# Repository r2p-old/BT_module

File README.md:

Bluetooth module 
==========

The R2P Bluetooth module.

### Hardware

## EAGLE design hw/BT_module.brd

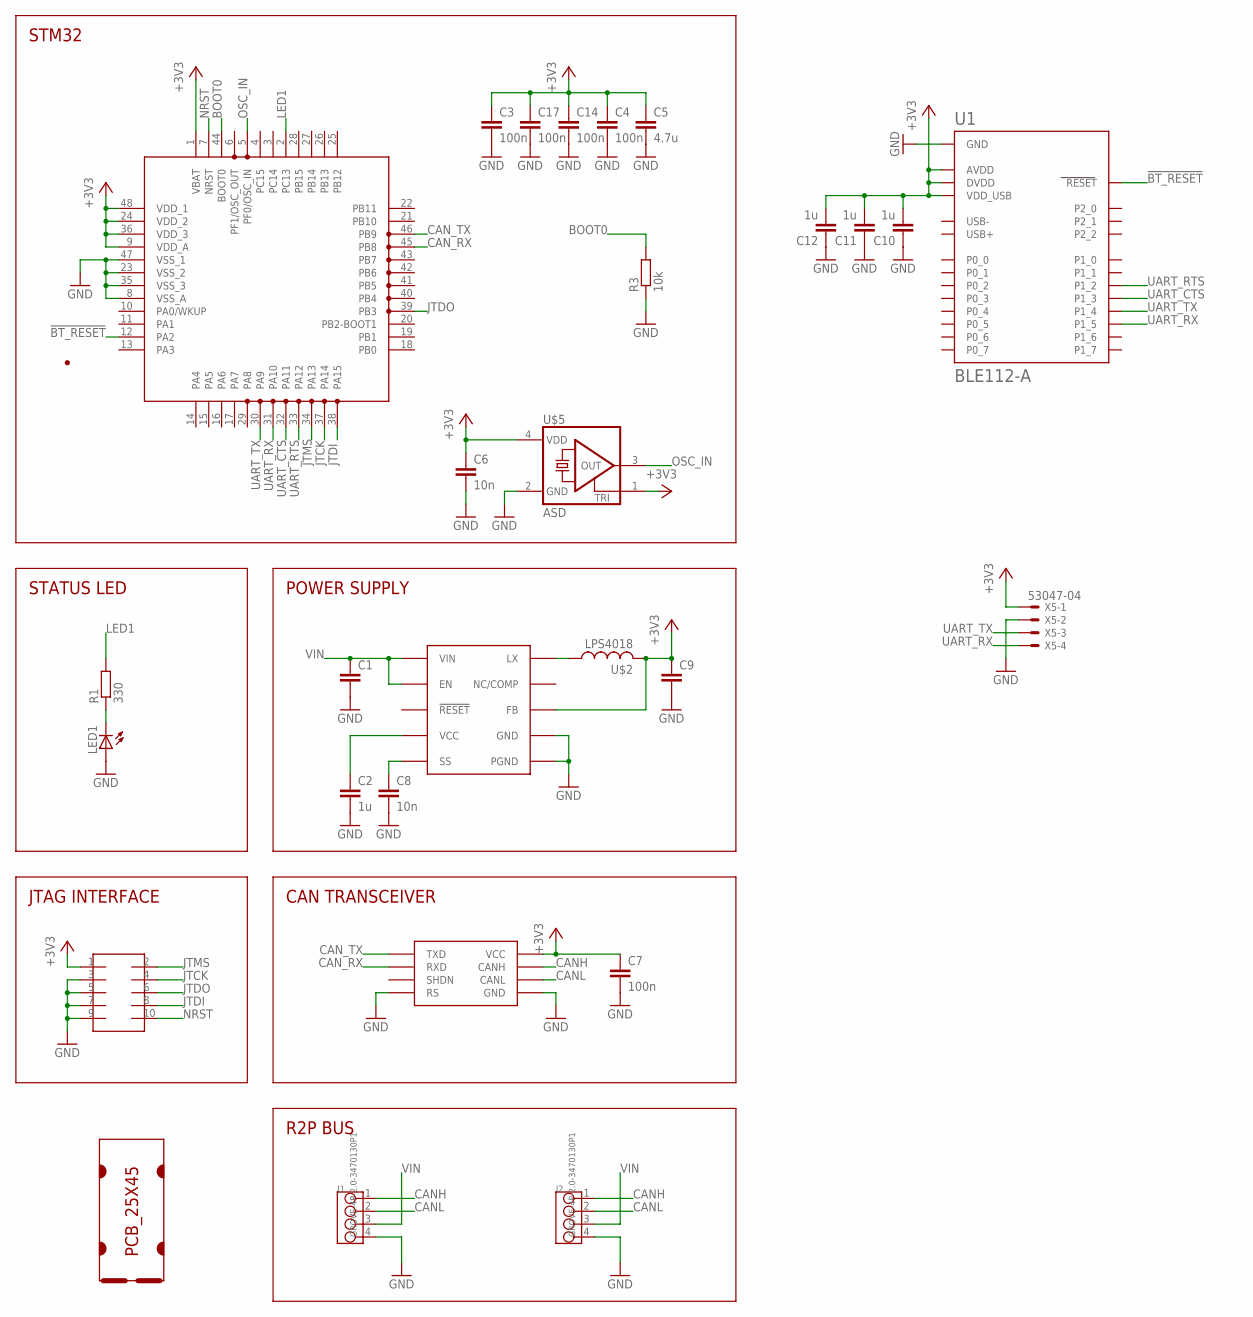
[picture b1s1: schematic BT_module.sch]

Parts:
C1: C-EUC1206; C1206
C2, C10, C11, C12: 1u; C0603
C3, C4, C7, C14, C17: 100n; C0603
C5: 4.7u; C0805
C6, C8: 10n; C0603
C9: C-EUC0805; C0805
J1, J2: GROVE-4P-2.0-3470130P1; 4P-2.0
LED1: LEDCHIPLED_0805; CHIPLED_0805
R1: 330; R0603
R3: 10k; R0603
SOT1: MAX3051EKA; SOT23-8L
U1: BLE112-A
U$1: PCB_25X45; 25X45
U$2: LPS4018
U$3: MAX17501; TDFN-10
U$4: FTSH-105TH; FTSH-105-TH
U$5: ASD; 2.5X2
U$6: STM32F303C; LQFP48
X5: 53047-04

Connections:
!BT_RESET: U1.RESET, U$6.12 (PA2)
+3V3: C3.1, C4.1, C5.1, C6.1, C7.1, C9.1, C10.2, C11.2, C12.2, C14.1, C17.1, SOT1.3 (VCC), U1.AVDD, U1.AVDD@2 (AVDD), U1.DVDD, U1.VDD_USB, U$2.P$2 (2), U$3.P$5 (FB), U$4.1, U$5.1 (TRI), U$5.4 (VDD), U$6.1 (VBAT), U$6.9 (VDD_A), U$6.24 (VDD_2), U$6.36 (VDD_3), U$6.48 (VDD_1), X5.1
BOOT0: R3.2, U$6.44 (BOOT0)
CANH: J1.1, J2.1, SOT1.7 (CANH)
CANL: J1.2, J2.2, SOT1.6 (CANL)
CAN_RX: SOT1.4 (RXD), U$6.45 (PB8)
CAN_TX: SOT1.1 (TXD), U$6.46 (PB9)
GND: C1.2, C2.2, C3.2, C4.2, C5.2, C6.2, C7.2, C8.2, C9.2, C10.1, C11.1, C12.1, C14.2, C17.2, J1.4, J2.4, LED1.A, R3.1, SOT1.2 (GND), SOT1.8 (RS), U1.GND, U1.GND@2 (GND), U1.GND@3 (GND), U1.GND@4 (GND), U$3.P$1 (PGND), U$3.P$9 (GND), U$3.P$11 (PGND), U$4.3, U$4.5, U$4.7, U$4.9, U$5.2 (GND), U$6.8 (VSS_A), U$6.23 (VSS_2), U$6.35 (VSS_3), U$6.47 (VSS_1), X5.2
JTCK: U$4.4, U$6.37 (PA14)
JTDI: U$4.8, U$6.38 (PA15)
JTDO: U$4.6, U$6.39 (PB3)
JTMS: U$4.2, U$6.34 (PA13)
LED1: R1.2, U$6.2 (PC13)
unnamed: U$2.P$1 (1), U$3.P$10 (LX)
unnamed: LED1.C, R1.1
unnamed: C2.1, U$3.P$4 (VCC)
unnamed: C8.1, U$3.P$6 (SS)
NRST: U$4.10, U$6.7 (NRST)
OSC_IN: U$5.3 (OUT), U$6.5 (PF0/OSC_IN)
UART_CTS: U1.P1_3, U$6.32 (PA11)
UART_RTS: U1.P1_2, U$6.33 (PA12)
UART_RX: U1.P1_5, U$6.31 (PA10), X5.4
UART_TX: U1.P1_4, U$6.30 (PA9), X5.3
VIN: C1.1, J1.3, J2.3, U$3.P$2 (VIN), U$3.P$3 (EN)

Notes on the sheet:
STM32
STATUS LED
JTAG INTERFACE
POWER SUPPLY
CAN TRANSCEIVER
R2P BUS

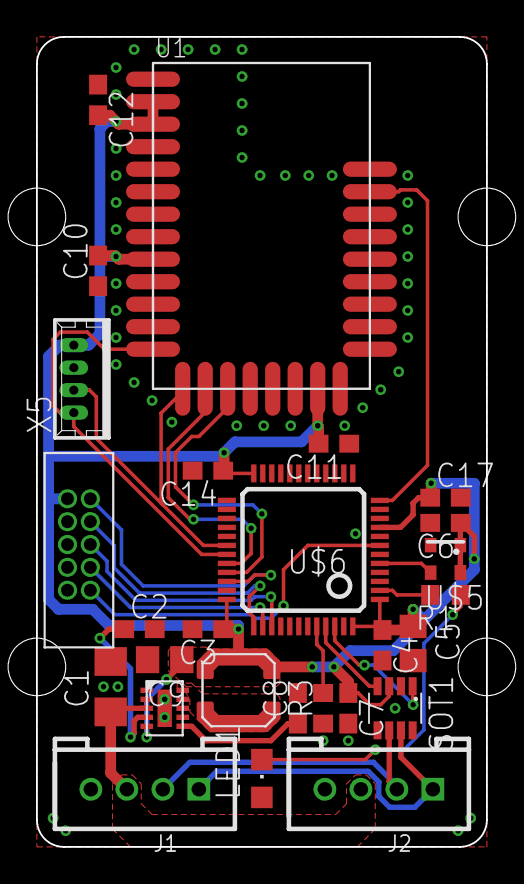
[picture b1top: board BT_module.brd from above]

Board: 2 copper layers, 25.0 x 45.0 mm, 28 parts (0 on the bottom side), 24 nets.

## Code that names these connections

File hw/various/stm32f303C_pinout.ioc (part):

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Mcu.Name=STM32F303C(B-C)Tx
Mcu.Package=LQFP48
Mcu.UserName=STM32F303CBTx
PA10.Mode=Asynchronous
PA10.Signal=USART1_RX
PA11.Mode=CTS_RTS
PA11.Signal=USART1_CTS
PA12.Mode=CTS_RTS
PA12.Signal=USART1_RTS
PA13.Mode=JTAG(4-pin)
PA13.Signal=SYS_JTMS-SWDIO
PA14.Mode=JTAG(4-pin)
PA14.Signal=SYS_JTCK-SWCLK
PA15.Mode=JTAG(4-pin)
PA15.Signal=SYS_JTDI
PA9.Mode=Asynchronous
PA9.Signal=USART1_TX
PB3.Mode=JTAG(4-pin)
PB3.Signal=SYS_JTDO-TRACESWO
PB8.Mode=Master
PB8.Signal=CAN_RX
PB9.Mode=Master
PB9.Signal=CAN_TX
PF0-OSC_IN.Signal=SYS_OSC_IN
PF1-OSC_OUT.GPIOParameters=GPIO_Label
PF1-OSC_OUT.GPIO_Label=LED
PF1-OSC_OUT.Signal=GPIO_Output

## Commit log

2014-06-11 layout completed
2014-06-13 final revision
2014-06-23 Added makefile for quicker gerber generation
2014-06-23 added documentation files
2014-06-24 added PNG of board layout
